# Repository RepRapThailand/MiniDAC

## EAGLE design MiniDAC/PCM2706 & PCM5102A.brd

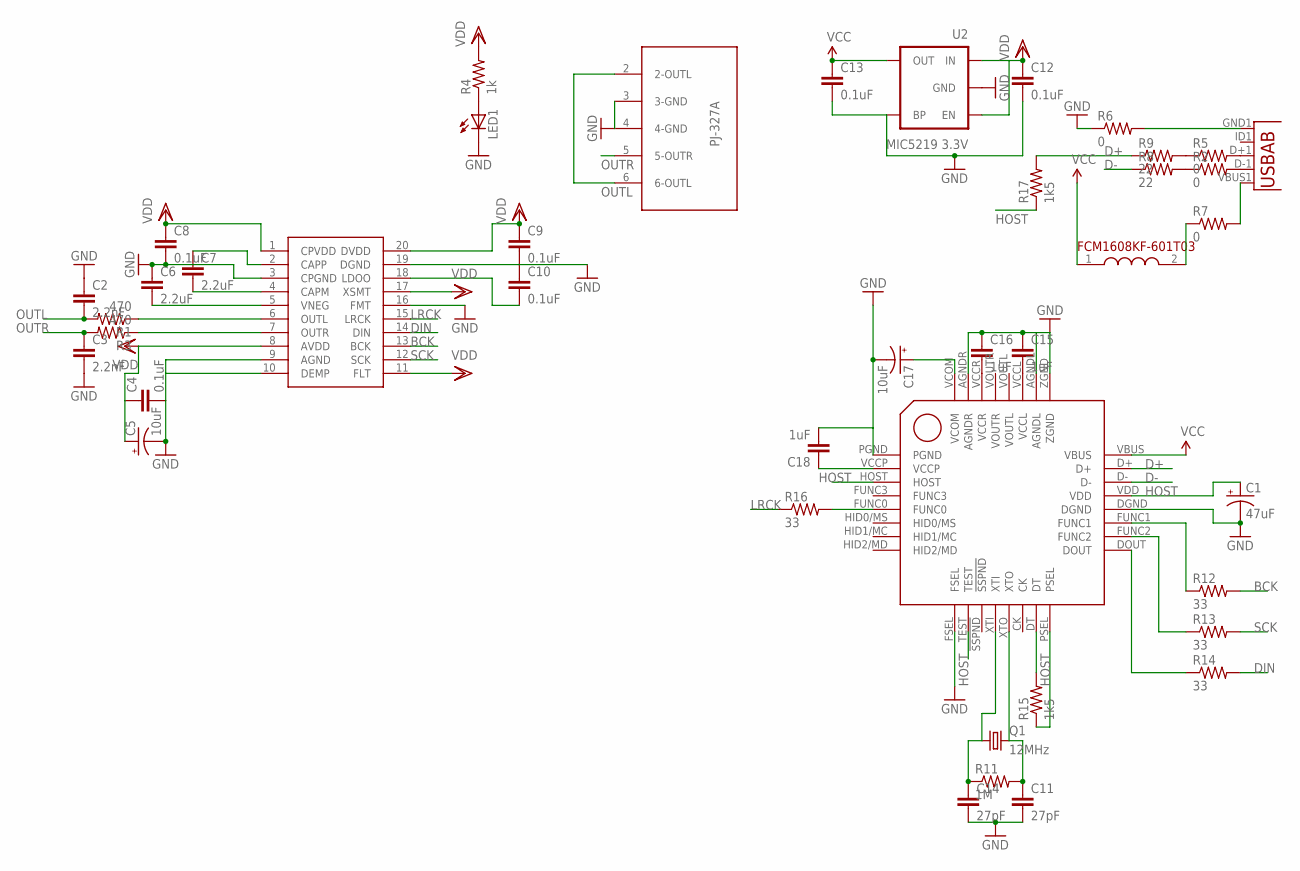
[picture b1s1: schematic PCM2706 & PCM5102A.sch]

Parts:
C1: 47uF; NIPPON_F80
C2, C3: 2.2nF; C5B2.5
C4, C8, C9, C10, C12, C13: 0.1uF; 1206
C5, C17: 10uF; NIPPON_F80
C6, C7: 2.2uF; 1206
C11, C14: 27pF; 1206
C15, C16, C18: 1uF; 1206
LED1: LEDCHIP-LED0805; CHIP-LED0805
Q1: 12MHz; SM49
R1, R3: 470; 1206
R2, R5, R6, R7: 0; 0805
R4: 1k; 1206
R8, R9: 22; 0805
R11: 1M; 0805
R12, R13, R14, R16: 33; 0805
R15, R17: 1k5; 0805
U1: USB""; USB-MICRO-SMD
U2: MIC5219 3.3V; SOT23-5
U$1: PCM5102; TSSOP20
U$2: PJ-327A
U$3: PCM2706; TQFP32-08
U$4: FCM1608KF-601T03

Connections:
BCK: R12.2, U$1.13 (BCK)
D+: R9.1, R17.2, U$3.D+
D-: R8.1, U$3.D-
DIN: R14.2, U$1.14 (DIN)
GND: C1.-, C2.1, C3.2, C4.2, C5.-, C6.1, C8.2, C9.2, C10.1, C11.2, C12.2, C13.2, C14.2, C15.1, C16.1, C17.-, C18.2, LED1.C, R6.1, U2.2 (GND), U2.4 (BP), U$1.3 (CPGND), U$1.9 (AGND), U$1.10 (DEMP), U$1.16 (FMT), U$1.19 (DGND), U$2.3 (3-GND), U$2.4 (4-GND), U$3.AGNDL, U$3.AGNDR, U$3.DGND, U$3.FSEL, U$3.PGND, U$3.ZGND
HOST: C1.+, R15.1, R17.1, U$3.HOST, U$3.PSEL, U$3.TEST, U$3.VDD
LRCK: R16.1, U$1.15 (LRCK)
unnamed: C7.1, U$1.2 (CAPP)
unnamed: LED1.A, R4.1
unnamed: R7.2, U1.VBUS1 (VBUS)
unnamed: R2.2, U1.D-1 (D-)
unnamed: R5.2, U1.D+1 (D+)
unnamed: C7.2, U$1.4 (CAPM)
unnamed: R3.1, U$1.7 (OUTR)
unnamed: R1.1, U$1.6 (OUTL)
unnamed: C6.2, U$1.5 (VNEG)
unnamed: C10.2, U$1.18 (LDOO)
unnamed: R7.1, U$4.2 (2.OUT)
unnamed: R6.2, U1.GND1 (GND)
unnamed: R5.1, R9.2
unnamed: R2.1, R8.2
unnamed: C14.1, Q1.1, R11.1, U$3.XTI
unnamed: C11.1, Q1.2, R11.2, U$3.XTO
unnamed: R15.2, U$3.DT
unnamed: R14.1, U$3.DOUT
unnamed: R13.1, U$3.FUNC2
unnamed: R12.1, U$3.FUNC1
unnamed: C15.2, U$3.VCCL
unnamed: R16.2, U$3.FUNC0
unnamed: C16.2, U$3.VCCR
unnamed: C17.+, U$3.VCOM
unnamed: C18.1, U$3.VCCP
OUTL: C2.2, R1.2, U$2.2 (2-OUTL), U$2.6 (6-OUTL)
OUTR: C3.1, R3.2, U$2.5 (5-OUTR)
SCK: R13.2, U$1.12 (SCK)
VCC: C13.1, U2.5 (OUT), U$3.VBUS, U$4.1 (1.IN)
VDD: C4.1, C5.+, C8.1, C9.1, C12.1, R4.2, U2.1 (IN), U2.3 (EN), U$1.1 (CPVDD), U$1.8 (AVDD), U$1.11 (FLT), U$1.17 (XSMT), U$1.20 (DVDD)

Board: 2 copper layers, 42 parts (20 on the bottom side), 37 nets, no tracks yet.

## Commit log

2016-04-24 ver1.0.0

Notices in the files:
parts and their libraries:
SparkFun-PowerIC: Licensing: CC v3.0 Share-Alike You are welcome to use this library for commercial purposes.
